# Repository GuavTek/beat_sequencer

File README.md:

A MIDI sequencer for percussion using a RP-PICO, WS2812 LEDs, and cherry style keyboard switches

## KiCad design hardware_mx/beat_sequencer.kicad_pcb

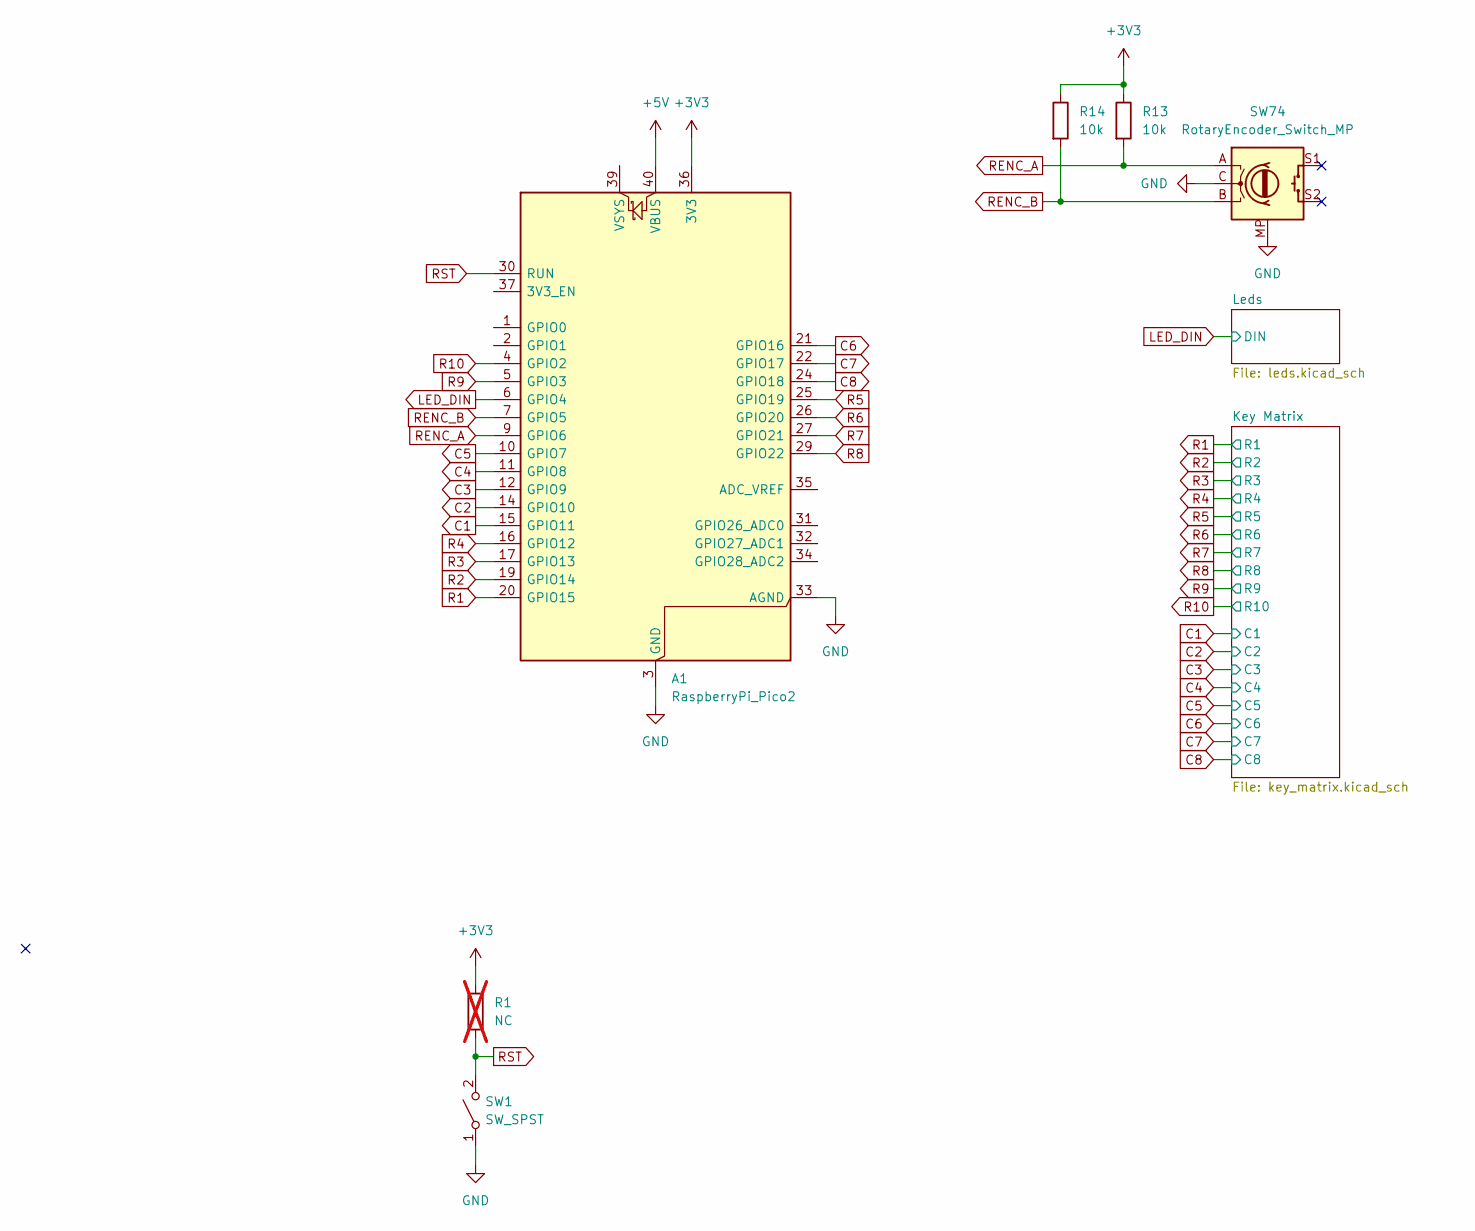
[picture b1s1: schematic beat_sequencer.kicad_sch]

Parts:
A1: RaspberryPi_Pico2; RaspberryPi_Pico_Common_SMD
R1: NC; R_0603_1608Metric; not fitted
R13, R14: 10k; R_0603_1608Metric
SW1: SW_SPST; SW_PUSH_6mm
SW74: RotaryEncoder_Switch_MP; RotaryEncoder_Alps_EC12E_Vertical_H20mm

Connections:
+3V3: A1.36 (3V3), R1.1, R13.1, R14.1; also elsewhere on the board
+5V: A1.40 (VBUS); also elsewhere on the board
C1: A1.15 (GPIO11); also elsewhere on the board
C2: A1.14 (GPIO10); also elsewhere on the board
C3: A1.12 (GPIO9); also elsewhere on the board
C4: A1.11 (GPIO8); also elsewhere on the board
C5: A1.10 (GPIO7); also elsewhere on the board
C6: A1.21 (GPIO16); also elsewhere on the board
C7: A1.22 (GPIO17); also elsewhere on the board
C8: A1.24 (GPIO18); also elsewhere on the board
GND: A1.3 (GND), A1.8 (GND), A1.13 (GND), A1.18 (GND), A1.23 (GND), A1.28 (GND), A1.33 (AGND), A1.38 (GND), SW1.1 (A), SW74.C, SW74.MP; also elsewhere on the board
LED_DIN: A1.6 (GPIO4); also elsewhere on the board
R1: A1.20 (GPIO15); also elsewhere on the board
R2: A1.19 (GPIO14); also elsewhere on the board
R3: A1.17 (GPIO13); also elsewhere on the board
R4: A1.16 (GPIO12); also elsewhere on the board
R5: A1.25 (GPIO19); also elsewhere on the board
R6: A1.26 (GPIO20); also elsewhere on the board
R7: A1.27 (GPIO21); also elsewhere on the board
R8: A1.29 (GPIO22); also elsewhere on the board
R9: A1.5 (GPIO3); also elsewhere on the board
R10: A1.4 (GPIO2); also elsewhere on the board
RENC_A: A1.9 (GPIO6), R13.2, SW74.A
RENC_B: A1.7 (GPIO5), R14.2, SW74.B
RST: A1.30 (RUN), R1.2, SW1.2 (B)

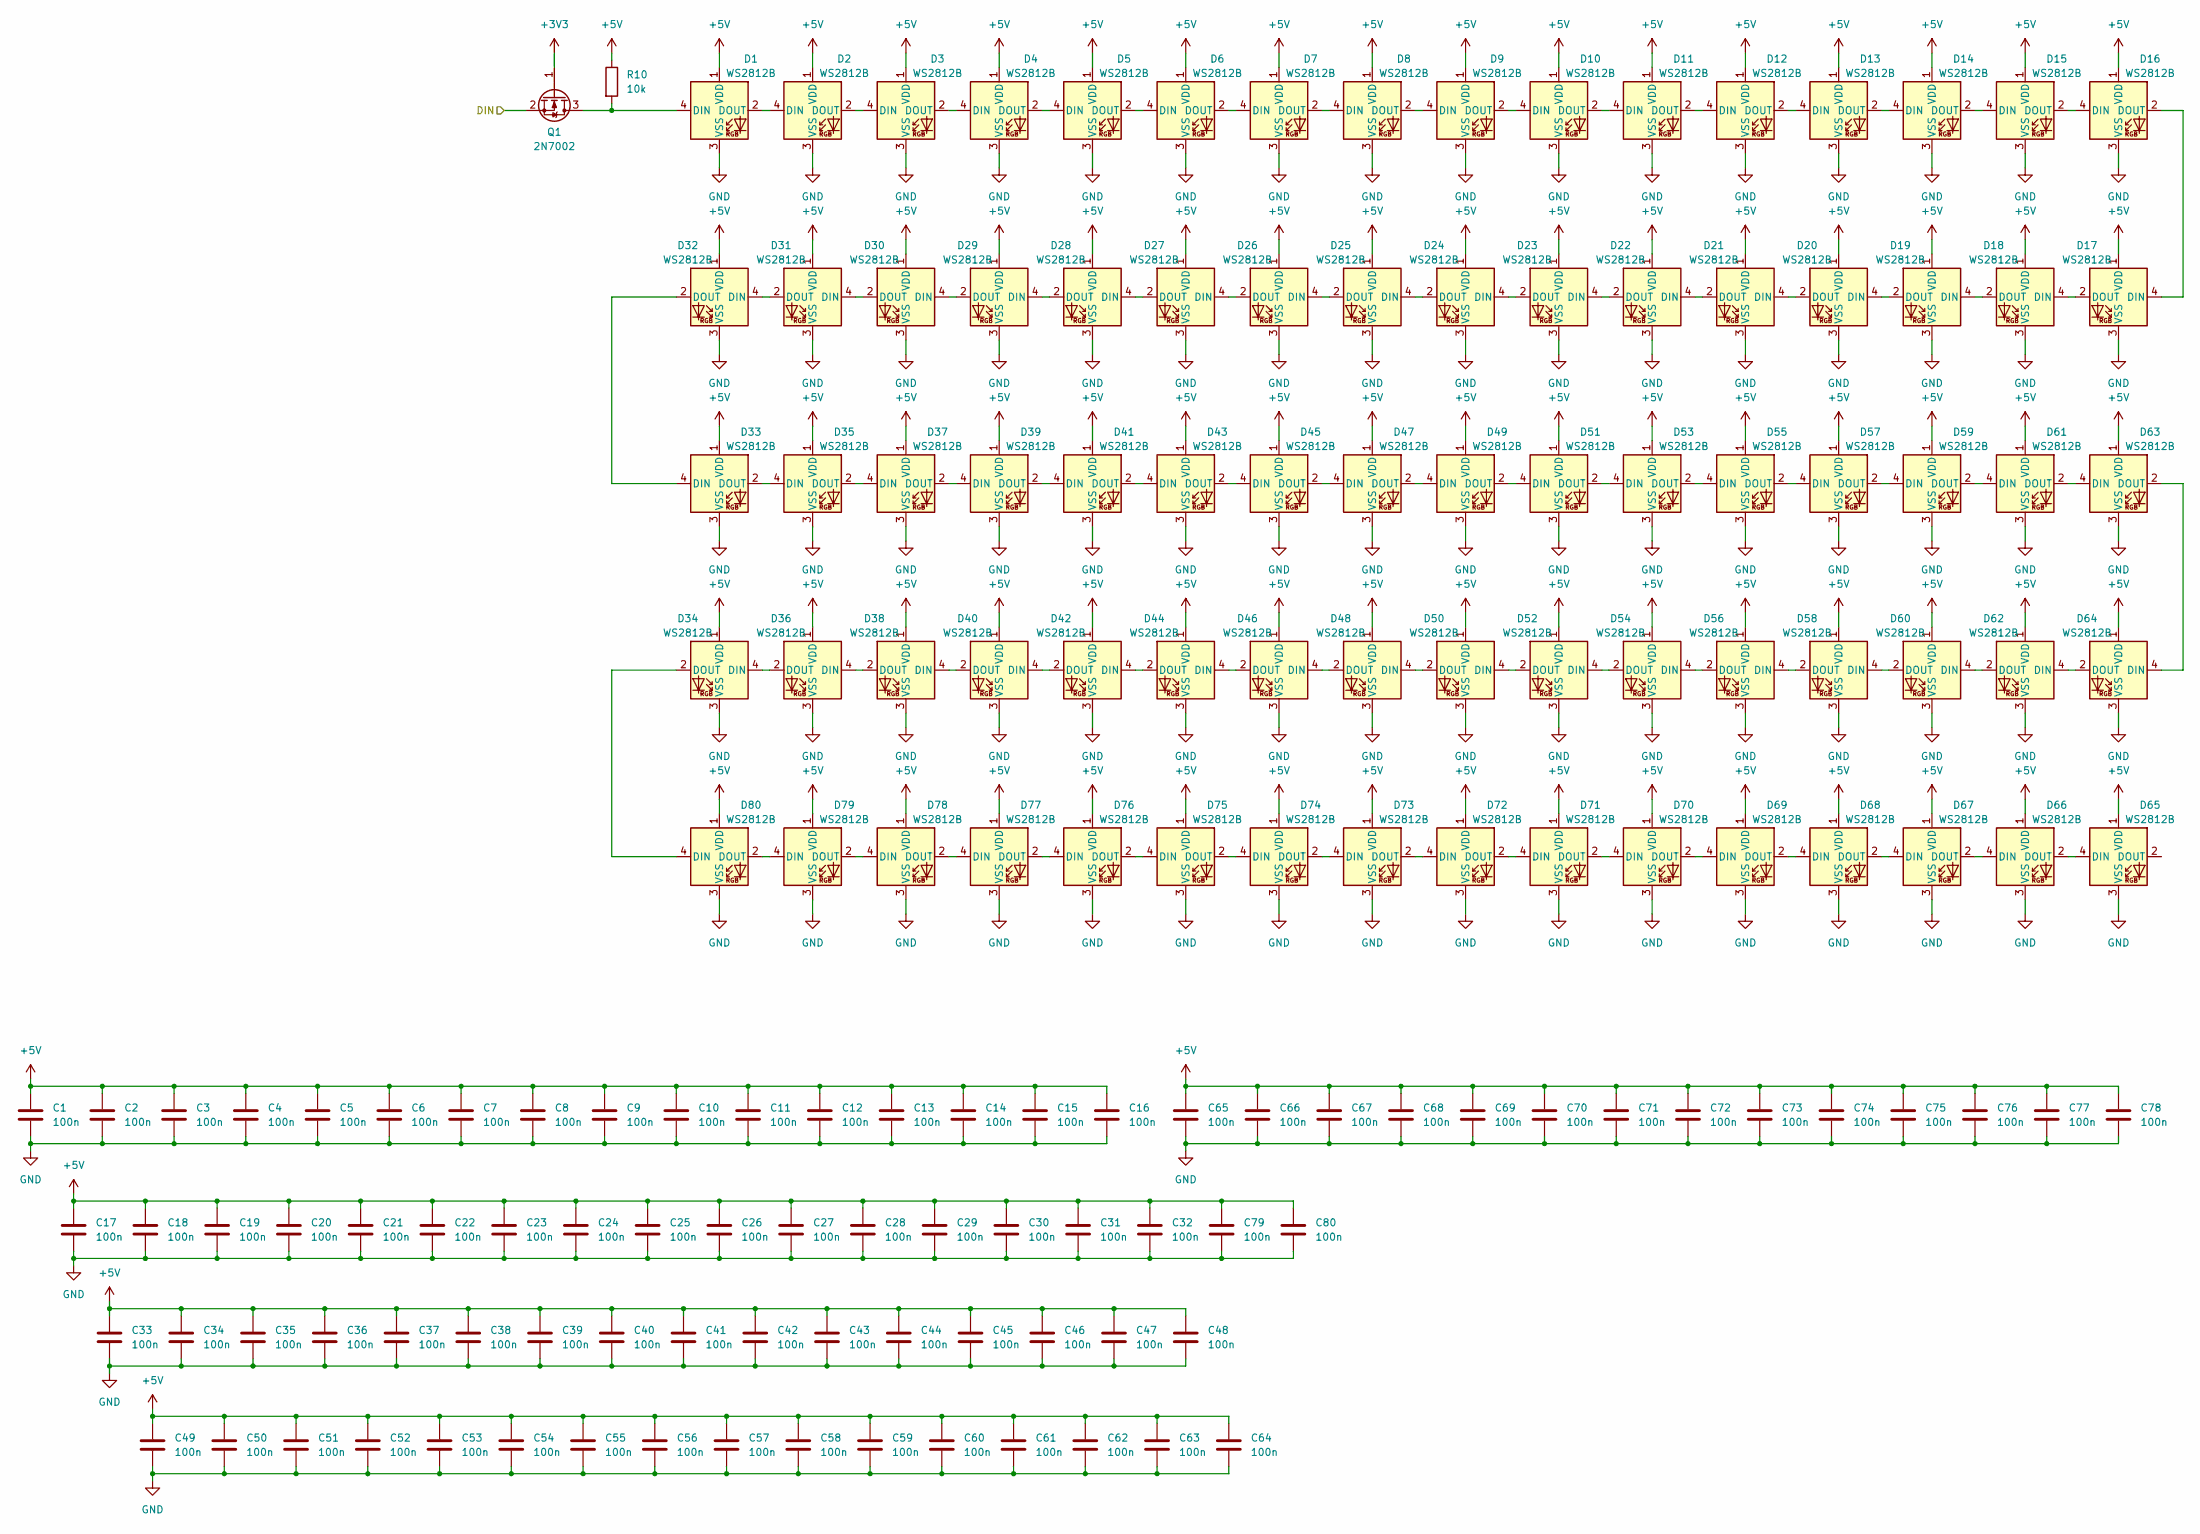
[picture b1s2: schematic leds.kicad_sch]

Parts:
C1, C2, C3, C4, C5, C6, C7, C8, C9, C10, C11, C12, C13, C14, C15, C16, C17, C18, C19, C20, C21, C22, C23, C24, C25, C26, C27, C28, C29, C30, C31, C32, C33, C34, C35, C36, C37, C38, C39, C40, C41, C42, C43, C44, C45, C46, C47, C48, C49, C50, C51, C52, C53, C54, C55, C56, C57, C58, C59, C60, C61, C62, C63, C64, C65, C66, C67, C68, C69, C70, C71, C72, C73, C74, C75, C76, C77, C78, C79, C80: 100n; C_0603_1608Metric
D1, D2, D3, D4, D5, D6, D7, D8, D9, D10, D11, D12, D13, D14, D15, D16, D17, D18, D19, D20, D21, D22, D23, D24, D25, D26, D27, D28, D29, D30, D31, D32, D33, D34, D35, D36, D37, D38, D39, D40, D41, D42, D43, D44, D45, D46, D47, D48, D49, D50, D51, D52, D53, D54, D55, D56, D57, D58, D59, D60, D61, D62, D63, D64, D65, D66, D67, D68, D69, D70, D71, D72, D73, D74, D75, D76, D77, D78, D79, D80: WS2812B; LED_SK6812_MINI_REVERSE
Q1: 2N7002; SOT-23
R10: 10k; R_0603_1608Metric

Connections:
+3V3: Q1.1 (G); also elsewhere on the board
+5V: C1.1, C2.1, C3.1, C4.1, C5.1, C6.1, C7.1, C8.1, C9.1, C10.1, C11.1, C12.1, C13.1, C14.1, C15.1, C16.1, C17.1, C18.1, C19.1, C20.1, C21.1, C22.1, C23.1, C24.1, C25.1, C26.1, C27.1, C28.1, C29.1, C30.1, C31.1, C32.1, C33.1, C34.1, C35.1, C36.1, C37.1, C38.1, C39.1, C40.1, C41.1, C42.1, C43.1, C44.1, C45.1, C46.1, C47.1, C48.1, C49.1, C50.1, C51.1, C52.1, C53.1, C54.1, C55.1, C56.1, C57.1, C58.1, C59.1, C60.1, C61.1, C62.1, C63.1, C64.1, C65.1, C66.1, C67.1, C68.1, C69.1, C70.1, C71.1, C72.1, C73.1, C74.1, C75.1, C76.1, C77.1, C78.1, C79.1, C80.1, D1.1 (VDD), D2.1 (VDD), D3.1 (VDD), D4.1 (VDD), D5.1 (VDD), D6.1 (VDD), D7.1 (VDD), D8.1 (VDD), D9.1 (VDD), D10.1 (VDD), D11.1 (VDD), D12.1 (VDD), D13.1 (VDD), D14.1 (VDD), D15.1 (VDD), D16.1 (VDD), D17.1 (VDD), D18.1 (VDD), D19.1 (VDD), D20.1 (VDD), D21.1 (VDD), D22.1 (VDD), D23.1 (VDD), D24.1 (VDD), D25.1 (VDD), D26.1 (VDD), D27.1 (VDD), D28.1 (VDD), D29.1 (VDD), D30.1 (VDD), D31.1 (VDD), D32.1 (VDD), D33.1 (VDD), D34.1 (VDD), D35.1 (VDD), D36.1 (VDD), D37.1 (VDD), D38.1 (VDD), D39.1 (VDD), D40.1 (VDD), D41.1 (VDD), D42.1 (VDD), D43.1 (VDD), D44.1 (VDD), D45.1 (VDD), D46.1 (VDD), D47.1 (VDD), D48.1 (VDD), D49.1 (VDD), D50.1 (VDD), D51.1 (VDD), D52.1 (VDD), D53.1 (VDD), D54.1 (VDD), D55.1 (VDD), D56.1 (VDD), D57.1 (VDD), D58.1 (VDD), D59.1 (VDD), D60.1 (VDD), D61.1 (VDD), D62.1 (VDD), D63.1 (VDD), D64.1 (VDD), D65.1 (VDD), D66.1 (VDD), D67.1 (VDD), D68.1 (VDD), D69.1 (VDD), D70.1 (VDD), D71.1 (VDD), D72.1 (VDD), D73.1 (VDD), D74.1 (VDD), D75.1 (VDD), D76.1 (VDD), D77.1 (VDD), D78.1 (VDD), D79.1 (VDD), D80.1 (VDD), R10.1; also elsewhere on the board
GND: C1.2, C2.2, C3.2, C4.2, C5.2, C6.2, C7.2, C8.2, C9.2, C10.2, C11.2, C12.2, C13.2, C14.2, C15.2, C16.2, C17.2, C18.2, C19.2, C20.2, C21.2, C22.2, C23.2, C24.2, C25.2, C26.2, C27.2, C28.2, C29.2, C30.2, C31.2, C32.2, C33.2, C34.2, C35.2, C36.2, C37.2, C38.2, C39.2, C40.2, C41.2, C42.2, C43.2, C44.2, C45.2, C46.2, C47.2, C48.2, C49.2, C50.2, C51.2, C52.2, C53.2, C54.2, C55.2, C56.2, C57.2, C58.2, C59.2, C60.2, C61.2, C62.2, C63.2, C64.2, C65.2, C66.2, C67.2, C68.2, C69.2, C70.2, C71.2, C72.2, C73.2, C74.2, C75.2, C76.2, C77.2, C78.2, C79.2, C80.2, D1.3 (VSS), D2.3 (VSS), D3.3 (VSS), D4.3 (VSS), D5.3 (VSS), D6.3 (VSS), D7.3 (VSS), D8.3 (VSS), D9.3 (VSS), D10.3 (VSS), D11.3 (VSS), D12.3 (VSS), D13.3 (VSS), D14.3 (VSS), D15.3 (VSS), D16.3 (VSS), D17.3 (VSS), D18.3 (VSS), D19.3 (VSS), D20.3 (VSS), D21.3 (VSS), D22.3 (VSS), D23.3 (VSS), D24.3 (VSS), D25.3 (VSS), D26.3 (VSS), D27.3 (VSS), D28.3 (VSS), D29.3 (VSS), D30.3 (VSS), D31.3 (VSS), D32.3 (VSS), D33.3 (VSS), D34.3 (VSS), D35.3 (VSS), D36.3 (VSS), D37.3 (VSS), D38.3 (VSS), D39.3 (VSS), D40.3 (VSS), D41.3 (VSS), D42.3 (VSS), D43.3 (VSS), D44.3 (VSS), D45.3 (VSS), D46.3 (VSS), D47.3 (VSS), D48.3 (VSS), D49.3 (VSS), D50.3 (VSS), D51.3 (VSS), D52.3 (VSS), D53.3 (VSS), D54.3 (VSS), D55.3 (VSS), D56.3 (VSS), D57.3 (VSS), D58.3 (VSS), D59.3 (VSS), D60.3 (VSS), D61.3 (VSS), D62.3 (VSS), D63.3 (VSS), D64.3 (VSS), D65.3 (VSS), D66.3 (VSS), D67.3 (VSS), D68.3 (VSS), D69.3 (VSS), D70.3 (VSS), D71.3 (VSS), D72.3 (VSS), D73.3 (VSS), D74.3 (VSS), D75.3 (VSS), D76.3 (VSS), D77.3 (VSS), D78.3 (VSS), D79.3 (VSS), D80.3 (VSS); also elsewhere on the board
LED_DIN: Q1.2 (S); also elsewhere on the board
unnamed: D1.4 (DIN), Q1.3 (D), R10.2
unnamed: D1.2 (DOUT), D2.4 (DIN)
unnamed: D2.2 (DOUT), D3.4 (DIN)
unnamed: D3.2 (DOUT), D4.4 (DIN)
unnamed: D4.2 (DOUT), D5.4 (DIN)
unnamed: D5.2 (DOUT), D6.4 (DIN)
unnamed: D6.2 (DOUT), D7.4 (DIN)
unnamed: D7.2 (DOUT), D8.4 (DIN)
unnamed: D8.2 (DOUT), D9.4 (DIN)
unnamed: D9.2 (DOUT), D10.4 (DIN)
unnamed: D10.2 (DOUT), D11.4 (DIN)
unnamed: D11.2 (DOUT), D12.4 (DIN)
unnamed: D12.2 (DOUT), D13.4 (DIN)
unnamed: D13.2 (DOUT), D14.4 (DIN)
unnamed: D14.2 (DOUT), D15.4 (DIN)
unnamed: D15.2 (DOUT), D16.4 (DIN)
unnamed: D16.2 (DOUT), D17.4 (DIN)
unnamed: D17.2 (DOUT), D18.4 (DIN)
unnamed: D18.2 (DOUT), D19.4 (DIN)
unnamed: D19.2 (DOUT), D20.4 (DIN)
unnamed: D20.2 (DOUT), D21.4 (DIN)
unnamed: D21.2 (DOUT), D22.4 (DIN)
unnamed: D22.2 (DOUT), D23.4 (DIN)
unnamed: D23.2 (DOUT), D24.4 (DIN)
unnamed: D24.2 (DOUT), D25.4 (DIN)
unnamed: D25.2 (DOUT), D26.4 (DIN)
unnamed: D26.2 (DOUT), D27.4 (DIN)
unnamed: D27.2 (DOUT), D28.4 (DIN)
unnamed: D28.2 (DOUT), D29.4 (DIN)
unnamed: D29.2 (DOUT), D30.4 (DIN)
unnamed: D30.2 (DOUT), D31.4 (DIN)
unnamed: D31.2 (DOUT), D32.4 (DIN)
unnamed: D32.2 (DOUT), D33.4 (DIN)
unnamed: D33.2 (DOUT), D35.4 (DIN)
unnamed: D34.4 (DIN), D36.2 (DOUT)
unnamed: D34.2 (DOUT), D80.4 (DIN)
unnamed: D35.2 (DOUT), D37.4 (DIN)
unnamed: D36.4 (DIN), D38.2 (DOUT)
unnamed: D37.2 (DOUT), D39.4 (DIN)
unnamed: D38.4 (DIN), D40.2 (DOUT)
unnamed: D39.2 (DOUT), D41.4 (DIN)
unnamed: D40.4 (DIN), D42.2 (DOUT)
unnamed: D41.2 (DOUT), D43.4 (DIN)
unnamed: D42.4 (DIN), D44.2 (DOUT)
unnamed: D43.2 (DOUT), D45.4 (DIN)
unnamed: D44.4 (DIN), D46.2 (DOUT)
unnamed: D45.2 (DOUT), D47.4 (DIN)
unnamed: D46.4 (DIN), D48.2 (DOUT)
unnamed: D47.2 (DOUT), D49.4 (DIN)
unnamed: D48.4 (DIN), D50.2 (DOUT)
unnamed: D49.2 (DOUT), D51.4 (DIN)
unnamed: D50.4 (DIN), D52.2 (DOUT)
unnamed: D51.2 (DOUT), D53.4 (DIN)
unnamed: D52.4 (DIN), D54.2 (DOUT)
unnamed: D53.2 (DOUT), D55.4 (DIN)
unnamed: D54.4 (DIN), D56.2 (DOUT)
unnamed: D55.2 (DOUT), D57.4 (DIN)
unnamed: D56.4 (DIN), D58.2 (DOUT)
unnamed: D57.2 (DOUT), D59.4 (DIN)
unnamed: D58.4 (DIN), D60.2 (DOUT)
unnamed: D59.2 (DOUT), D61.4 (DIN)
unnamed: D60.4 (DIN), D62.2 (DOUT)
unnamed: D61.2 (DOUT), D63.4 (DIN)
unnamed: D62.4 (DIN), D64.2 (DOUT)
unnamed: D63.2 (DOUT), D64.4 (DIN)
unnamed: D65.4 (DIN), D66.2 (DOUT)
unnamed: D66.4 (DIN), D67.2 (DOUT)
unnamed: D67.4 (DIN), D68.2 (DOUT)
unnamed: D68.4 (DIN), D69.2 (DOUT)
unnamed: D69.4 (DIN), D70.2 (DOUT)
unnamed: D70.4 (DIN), D71.2 (DOUT)
unnamed: D71.4 (DIN), D72.2 (DOUT)
unnamed: D72.4 (DIN), D73.2 (DOUT)
unnamed: D73.4 (DIN), D74.2 (DOUT)
unnamed: D74.4 (DIN), D75.2 (DOUT)
unnamed: D75.4 (DIN), D76.2 (DOUT)
unnamed: D76.4 (DIN), D77.2 (DOUT)
unnamed: D77.4 (DIN), D78.2 (DOUT)
unnamed: D78.4 (DIN), D79.2 (DOUT)
unnamed: D79.4 (DIN), D80.2 (DOUT)

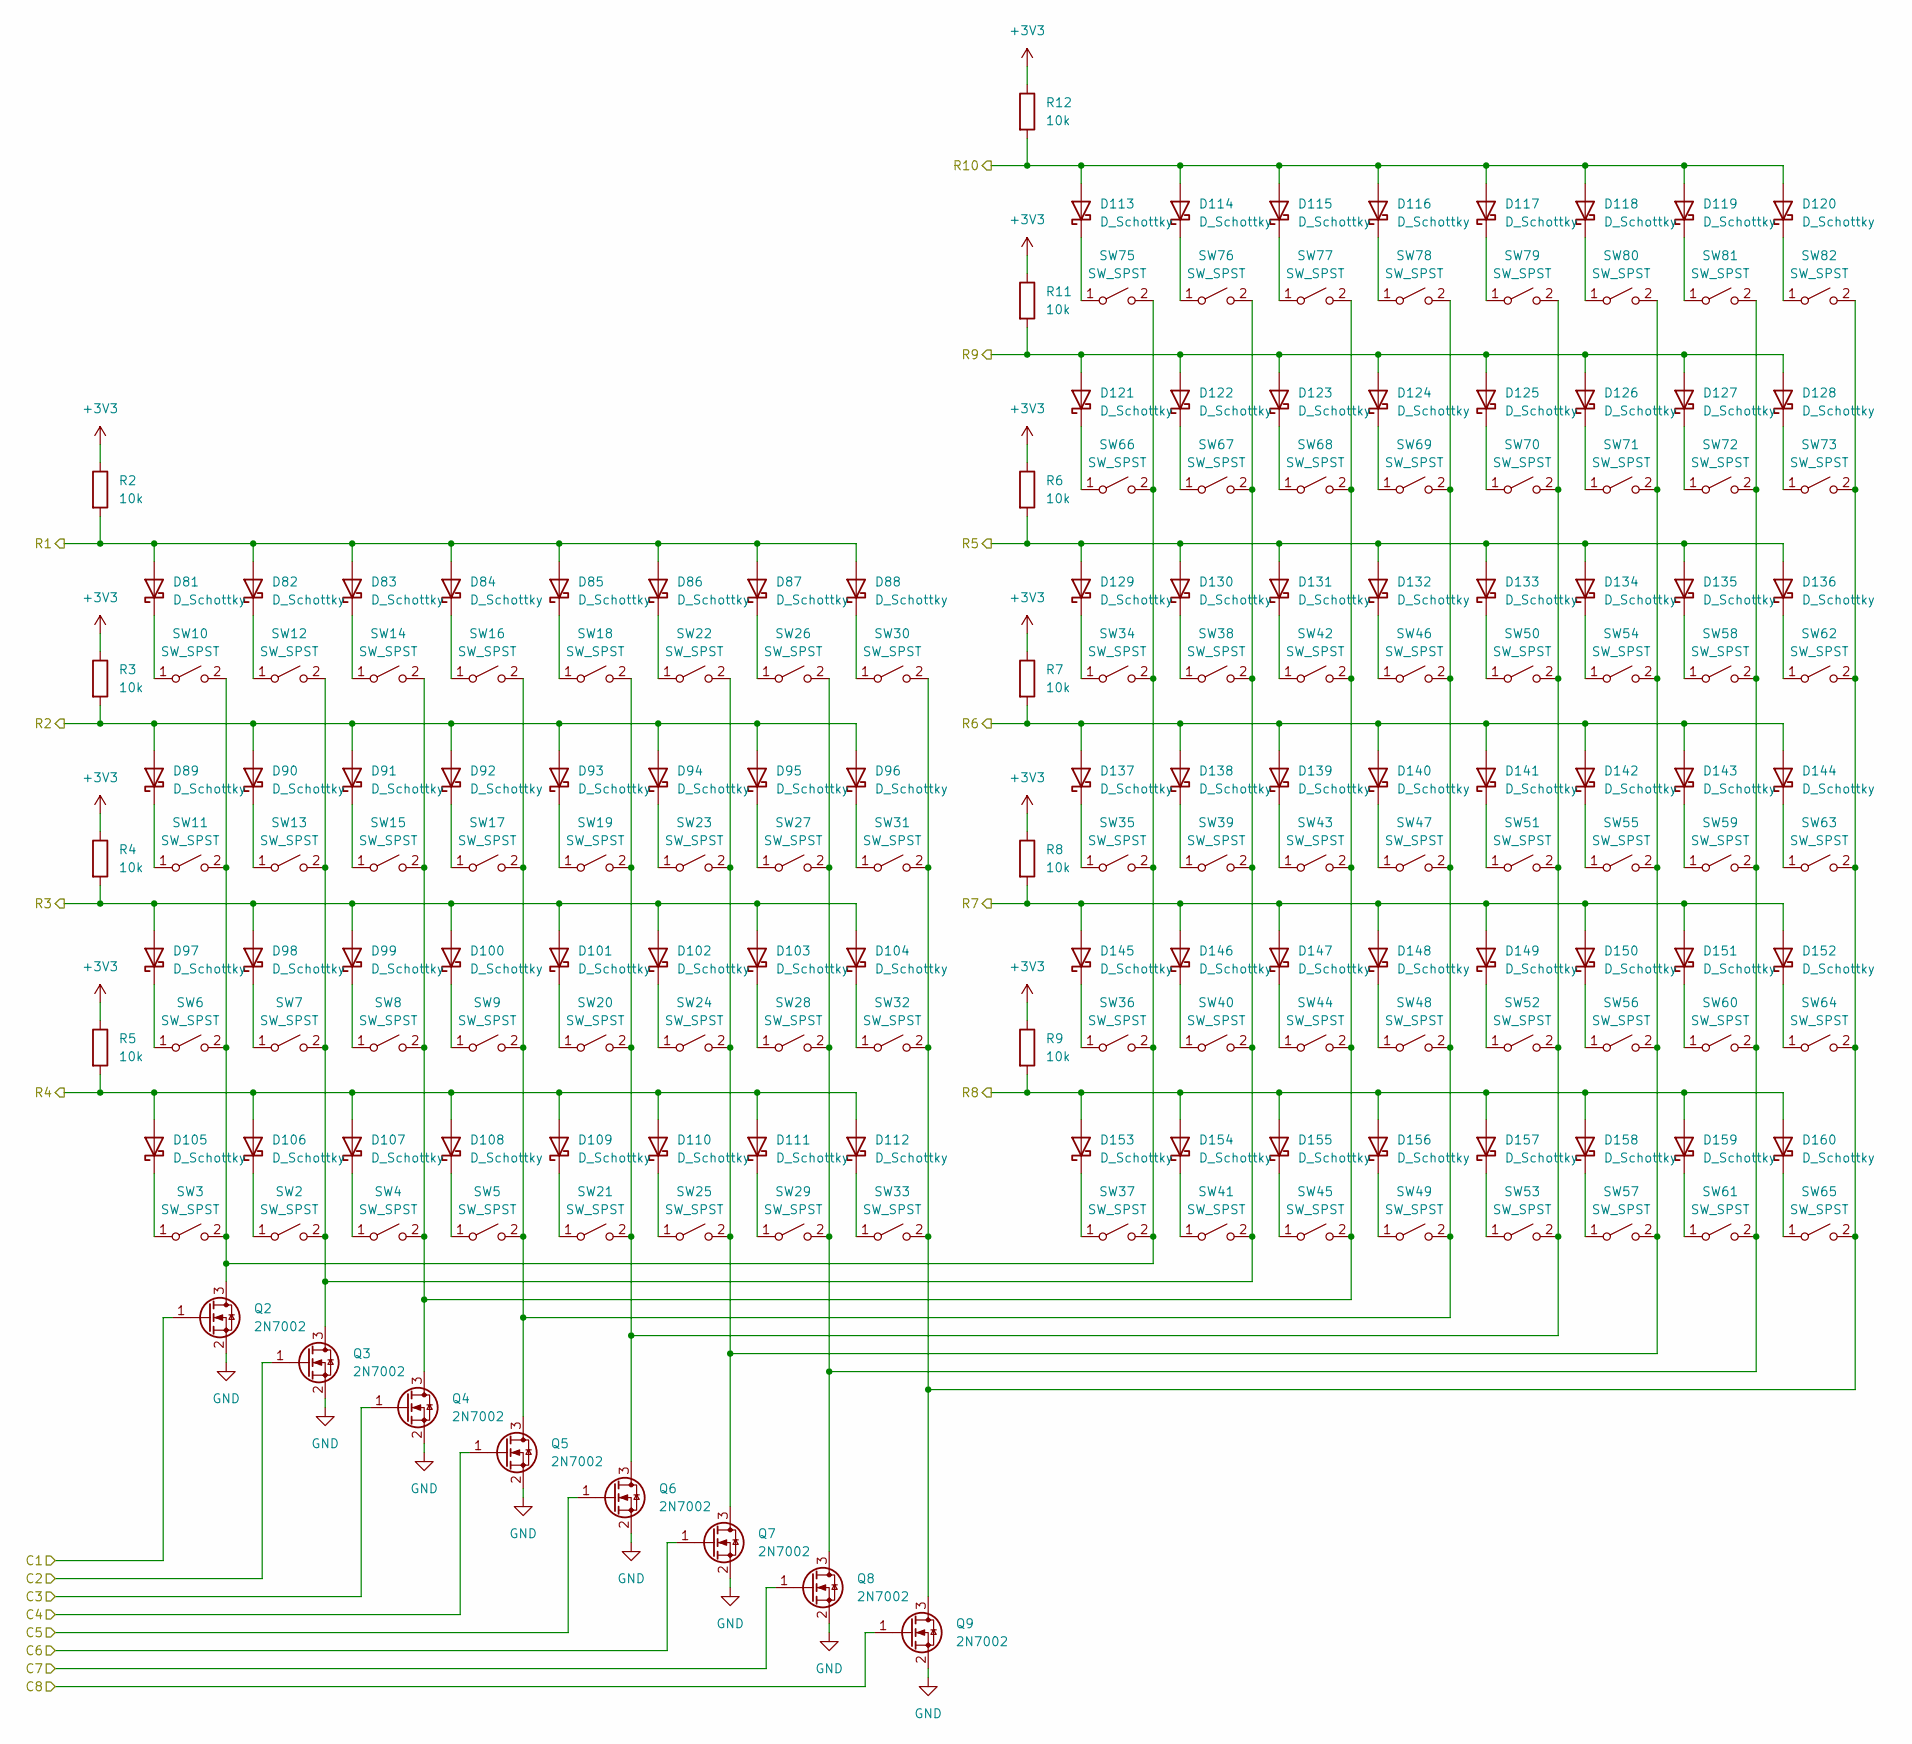
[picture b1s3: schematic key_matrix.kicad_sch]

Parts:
D81, D82, D83, D84, D85, D86, D87, D88, D89, D90, D91, D92, D93, D94, D95, D96, D97, D98, D99, D100, D101, D102, D103, D104, D105, D106, D107, D108, D109, D110, D111, D112, D113, D114, D115, D116, D117, D118, D119, D120, D121, D122, D123, D124, D125, D126, D127, D128, D129, D130, D131, D132, D133, D134, D135, D136, D137, D138, D139, D140, D141, D142, D143, D144, D145, D146, D147, D148, D149, D150, D151, D152, D153, D154, D155, D156, D157, D158, D159, D160: D_Schottky; D_SOD-323_HandSoldering
Q2, Q3, Q4, Q5, Q6, Q7, Q8, Q9: 2N7002; SOT-23
R2, R3, R4, R5, R6, R7, R8, R9, R11, R12: 10k; R_0603_1608Metric
SW2, SW3, SW4, SW5, SW6, SW7, SW8, SW9, SW10, SW11, SW12, SW13, SW14, SW15, SW16, SW17, SW18, SW19, SW20, SW21, SW22, SW23, SW24, SW25, SW26, SW27, SW28, SW29, SW30, SW31, SW32, SW33, SW34, SW35, SW36, SW37, SW38, SW39, SW40, SW41, SW42, SW43, SW44, SW45, SW46, SW47, SW48, SW49, SW50, SW51, SW52, SW53, SW54, SW55, SW56, SW57, SW58, SW59, SW60, SW61, SW62, SW63, SW64, SW65, SW66, SW67, SW68, SW69, SW70, SW71, SW72, SW73, SW75, SW76, SW77, SW78, SW79, SW80, SW81, SW82: SW_SPST; SW_Cherry_MX_1.00u_PCB

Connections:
+3V3: R2.1, R3.1, R4.1, R5.1, R6.1, R7.1, R8.1, R9.1, R11.1, R12.1; also elsewhere on the board
C1: Q2.1 (G); also elsewhere on the board
C2: Q3.1 (G); also elsewhere on the board
C3: Q4.1 (G); also elsewhere on the board
C4: Q5.1 (G); also elsewhere on the board
C5: Q6.1 (G); also elsewhere on the board
C6: Q7.1 (G); also elsewhere on the board
C7: Q8.1 (G); also elsewhere on the board
C8: Q9.1 (G); also elsewhere on the board
GND: Q2.2 (S), Q3.2 (S), Q4.2 (S), Q5.2 (S), Q6.2 (S), Q7.2 (S), Q8.2 (S), Q9.2 (S); also elsewhere on the board
unnamed: D81.1 (K), SW10.1 (A)
unnamed: D82.1 (K), SW12.1 (A)
unnamed: D83.1 (K), SW14.1 (A)
unnamed: D84.1 (K), SW16.1 (A)
unnamed: D85.1 (K), SW18.1 (A)
unnamed: D86.1 (K), SW22.1 (A)
unnamed: D87.1 (K), SW26.1 (A)
unnamed: D88.1 (K), SW30.1 (A)
unnamed: D89.1 (K), SW11.1 (A)
unnamed: D90.1 (K), SW13.1 (A)
unnamed: D91.1 (K), SW15.1 (A)
unnamed: D92.1 (K), SW17.1 (A)
unnamed: D93.1 (K), SW19.1 (A)
unnamed: D94.1 (K), SW23.1 (A)
unnamed: D95.1 (K), SW27.1 (A)
unnamed: D96.1 (K), SW31.1 (A)
unnamed: D97.1 (K), SW6.1 (A)
unnamed: D98.1 (K), SW7.1 (A)
unnamed: D99.1 (K), SW8.1 (A)
unnamed: D100.1 (K), SW9.1 (A)
unnamed: D101.1 (K), SW20.1 (A)
unnamed: D102.1 (K), SW24.1 (A)
unnamed: D103.1 (K), SW28.1 (A)
unnamed: D104.1 (K), SW32.1 (A)
unnamed: D105.1 (K), SW3.1 (A)
unnamed: D106.1 (K), SW2.1 (A)
unnamed: D107.1 (K), SW4.1 (A)
unnamed: D108.1 (K), SW5.1 (A)
unnamed: D109.1 (K), SW21.1 (A)
unnamed: D110.1 (K), SW25.1 (A)
unnamed: D111.1 (K), SW29.1 (A)
unnamed: D112.1 (K), SW33.1 (A)
unnamed: D113.1 (K), SW75.1 (A)
unnamed: D114.1 (K), SW76.1 (A)
unnamed: D115.1 (K), SW77.1 (A)
unnamed: D116.1 (K), SW78.1 (A)
unnamed: D117.1 (K), SW79.1 (A)
unnamed: D118.1 (K), SW80.1 (A)
unnamed: D119.1 (K), SW81.1 (A)
unnamed: D120.1 (K), SW82.1 (A)
unnamed: D121.1 (K), SW66.1 (A)
unnamed: D122.1 (K), SW67.1 (A)
unnamed: D123.1 (K), SW68.1 (A)
unnamed: D124.1 (K), SW69.1 (A)
unnamed: D125.1 (K), SW70.1 (A)
unnamed: D126.1 (K), SW71.1 (A)
unnamed: D127.1 (K), SW72.1 (A)
unnamed: D128.1 (K), SW73.1 (A)
unnamed: D129.1 (K), SW34.1 (A)
unnamed: D130.1 (K), SW38.1 (A)
unnamed: D131.1 (K), SW42.1 (A)
unnamed: D132.1 (K), SW46.1 (A)
unnamed: D133.1 (K), SW50.1 (A)
unnamed: D134.1 (K), SW54.1 (A)
unnamed: D135.1 (K), SW58.1 (A)
unnamed: D136.1 (K), SW62.1 (A)
unnamed: D137.1 (K), SW35.1 (A)
unnamed: D138.1 (K), SW39.1 (A)
unnamed: D139.1 (K), SW43.1 (A)
unnamed: D140.1 (K), SW47.1 (A)
unnamed: D141.1 (K), SW51.1 (A)
unnamed: D142.1 (K), SW55.1 (A)
unnamed: D143.1 (K), SW59.1 (A)
unnamed: D144.1 (K), SW63.1 (A)
unnamed: D145.1 (K), SW36.1 (A)
unnamed: D146.1 (K), SW40.1 (A)
unnamed: D147.1 (K), SW44.1 (A)
unnamed: D148.1 (K), SW48.1 (A)
unnamed: D149.1 (K), SW52.1 (A)
unnamed: D150.1 (K), SW56.1 (A)
unnamed: D151.1 (K), SW60.1 (A)
unnamed: D152.1 (K), SW64.1 (A)
unnamed: D153.1 (K), SW37.1 (A)
unnamed: D154.1 (K), SW41.1 (A)
unnamed: D155.1 (K), SW45.1 (A)
unnamed: D156.1 (K), SW49.1 (A)
unnamed: D157.1 (K), SW53.1 (A)
unnamed: D158.1 (K), SW57.1 (A)
unnamed: D159.1 (K), SW61.1 (A)
unnamed: D160.1 (K), SW65.1 (A)
unnamed: Q2.3 (D), SW3.2 (B), SW6.2 (B), SW10.2 (B), SW11.2 (B), SW34.2 (B), SW35.2 (B), SW36.2 (B), SW37.2 (B), SW66.2 (B), SW75.2 (B)
unnamed: Q3.3 (D), SW2.2 (B), SW7.2 (B), SW12.2 (B), SW13.2 (B), SW38.2 (B), SW39.2 (B), SW40.2 (B), SW41.2 (B), SW67.2 (B), SW76.2 (B)
unnamed: Q4.3 (D), SW4.2 (B), SW8.2 (B), SW14.2 (B), SW15.2 (B), SW42.2 (B), SW43.2 (B), SW44.2 (B), SW45.2 (B), SW68.2 (B), SW77.2 (B)
unnamed: Q5.3 (D), SW5.2 (B), SW9.2 (B), SW16.2 (B), SW17.2 (B), SW46.2 (B), SW47.2 (B), SW48.2 (B), SW49.2 (B), SW69.2 (B), SW78.2 (B)
unnamed: Q6.3 (D), SW18.2 (B), SW19.2 (B), SW20.2 (B), SW21.2 (B), SW50.2 (B), SW51.2 (B), SW52.2 (B), SW53.2 (B), SW70.2 (B), SW79.2 (B)
unnamed: Q7.3 (D), SW22.2 (B), SW23.2 (B), SW24.2 (B), SW25.2 (B), SW54.2 (B), SW55.2 (B), SW56.2 (B), SW57.2 (B), SW71.2 (B), SW80.2 (B)
unnamed: Q8.3 (D), SW26.2 (B), SW27.2 (B), SW28.2 (B), SW29.2 (B), SW58.2 (B), SW59.2 (B), SW60.2 (B), SW61.2 (B), SW72.2 (B), SW81.2 (B)
unnamed: Q9.3 (D), SW30.2 (B), SW31.2 (B), SW32.2 (B), SW33.2 (B), SW62.2 (B), SW63.2 (B), SW64.2 (B), SW65.2 (B), SW73.2 (B), SW82.2 (B)
R1: D81.2 (A), D82.2 (A), D83.2 (A), D84.2 (A), D85.2 (A), D86.2 (A), D87.2 (A), D88.2 (A), R2.2; also elsewhere on the board
R2: D89.2 (A), D90.2 (A), D91.2 (A), D92.2 (A), D93.2 (A), D94.2 (A), D95.2 (A), D96.2 (A), R3.2; also elsewhere on the board
R3: D97.2 (A), D98.2 (A), D99.2 (A), D100.2 (A), D101.2 (A), D102.2 (A), D103.2 (A), D104.2 (A), R4.2; also elsewhere on the board
R4: D105.2 (A), D106.2 (A), D107.2 (A), D108.2 (A), D109.2 (A), D110.2 (A), D111.2 (A), D112.2 (A), R5.2; also elsewhere on the board
R5: D129.2 (A), D130.2 (A), D131.2 (A), D132.2 (A), D133.2 (A), D134.2 (A), D135.2 (A), D136.2 (A), R6.2; also elsewhere on the board
R6: D137.2 (A), D138.2 (A), D139.2 (A), D140.2 (A), D141.2 (A), D142.2 (A), D143.2 (A), D144.2 (A), R7.2; also elsewhere on the board
R7: D145.2 (A), D146.2 (A), D147.2 (A), D148.2 (A), D149.2 (A), D150.2 (A), D151.2 (A), D152.2 (A), R8.2; also elsewhere on the board
R8: D153.2 (A), D154.2 (A), D155.2 (A), D156.2 (A), D157.2 (A), D158.2 (A), D159.2 (A), D160.2 (A), R9.2; also elsewhere on the board
R9: D121.2 (A), D122.2 (A), D123.2 (A), D124.2 (A), D125.2 (A), D126.2 (A), D127.2 (A), D128.2 (A), R11.2; also elsewhere on the board
R10: D113.2 (A), D114.2 (A), D115.2 (A), D116.2 (A), D117.2 (A), D118.2 (A), D119.2 (A), D120.2 (A), R12.2; also elsewhere on the board

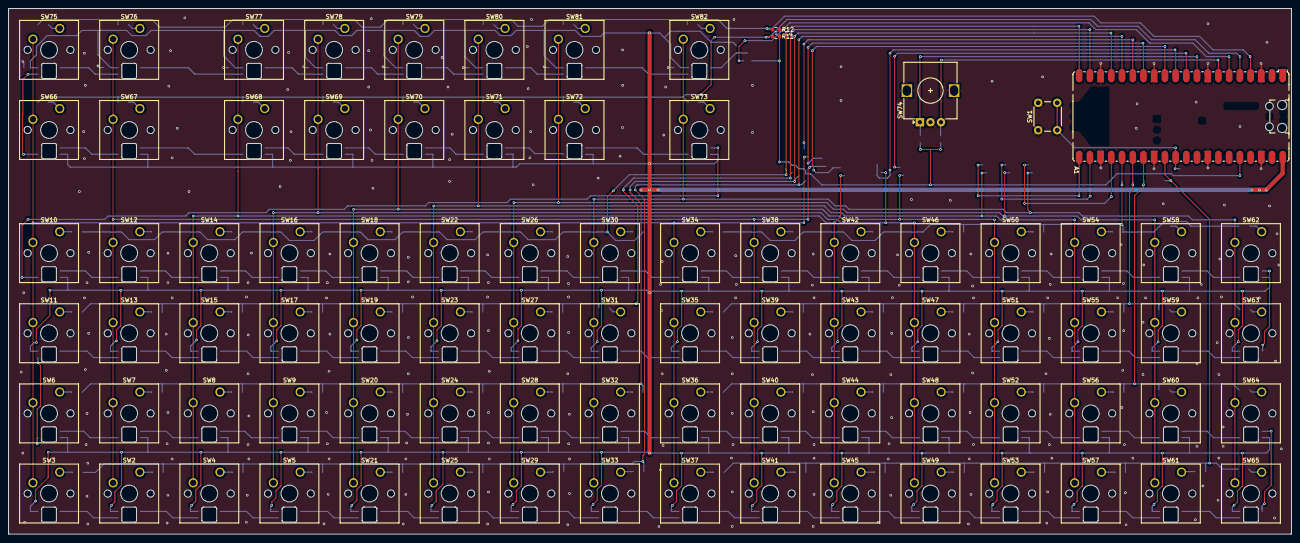
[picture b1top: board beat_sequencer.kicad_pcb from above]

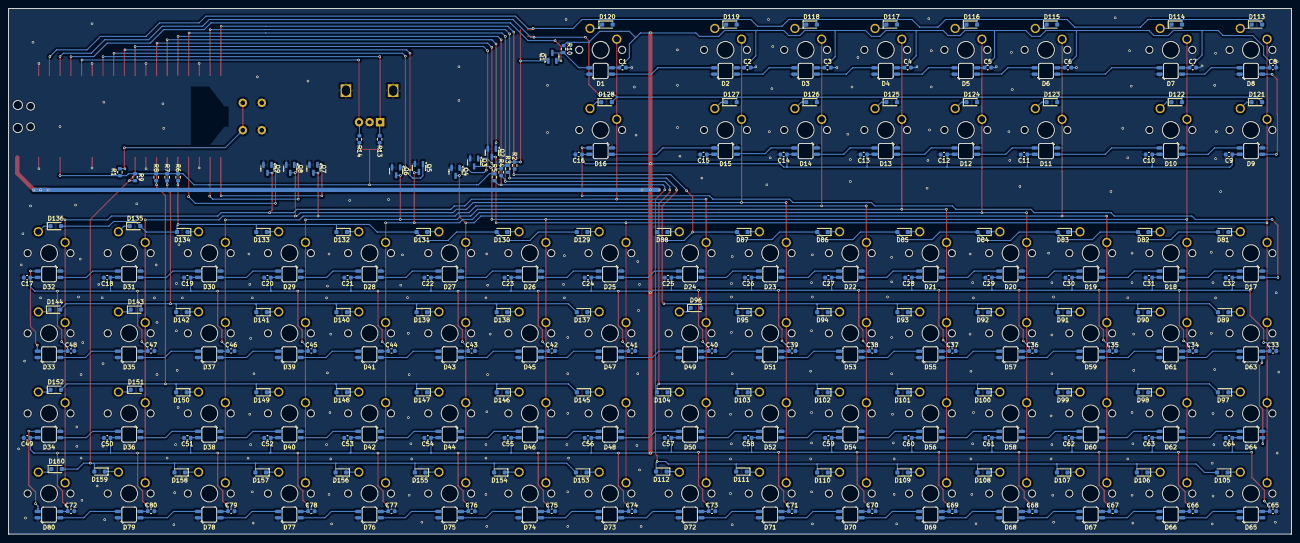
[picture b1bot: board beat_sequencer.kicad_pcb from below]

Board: 2 copper layers, 304.2 x 124.6 mm, 346 parts (261 on the bottom side), 193 nets.

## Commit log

2025-06-13 Add gitignore
2025-06-13 Add initial PCB
2025-06-13 Add ws2812 library
2025-06-13 Add temp code
2025-07-08 Implement functions for led array
2025-07-11 Read button states
2025-07-11 Add diodes to schematic to prevent ghosting
2025-07-11 Read rotary encoder
2025-07-11 Move rotary encoder handling to buttons.c
2025-07-11 Add USB midi
2025-07-12 Fix rotary encoder direction
2025-07-12 Add some basic sequencing
2025-07-13 Implement velocity multiplier to rotary encoder
2025-07-24 Rename hardware folder to specify switches
2025-07-24 Add hardware with choc switches
2025-07-27 Fix DFM errors
2025-07-29 Allow editing sequence after end step
2025-08-23 Add mosfets to columns
2025-08-23 Update pico partnumber
2025-08-23 Implement using MOSFETs on columns
2025-08-23 Add brackets model
2025-08-24 Add some tolerance to the slots
2025-09-22 Add step velocity
2025-09-22 Initialize arrays
2025-09-22 Add send_midi function
2026-02-24 Fix velocity presets overflowing
2026-02-24 Make bpm convertsion more accurate
2026-02-24 Fix sequencer freezing due to USB overflow
